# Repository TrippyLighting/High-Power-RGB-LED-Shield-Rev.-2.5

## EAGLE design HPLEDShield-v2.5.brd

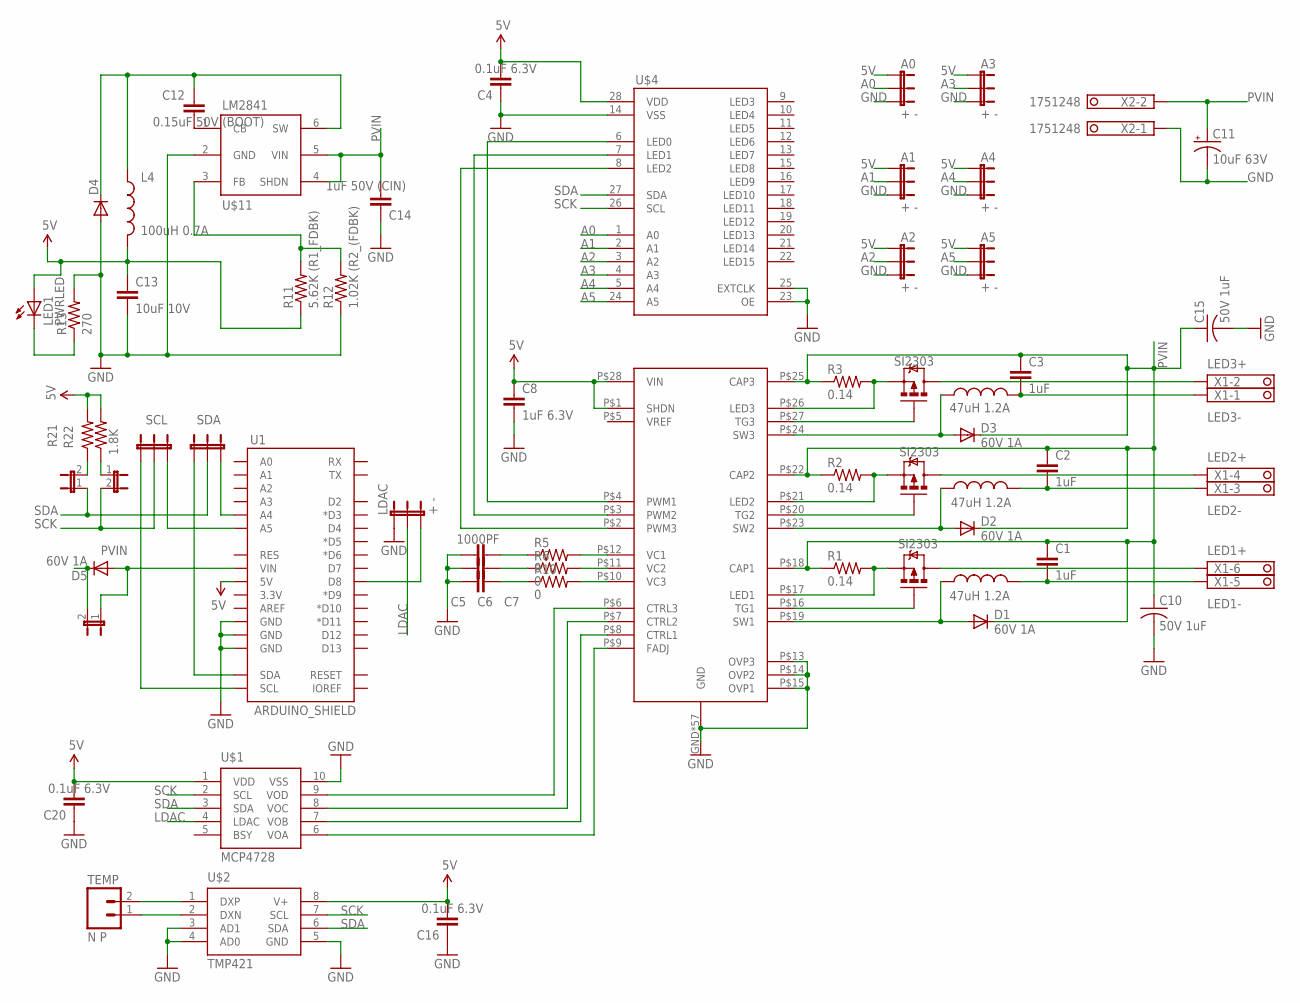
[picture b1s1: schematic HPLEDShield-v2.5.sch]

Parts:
A0, A1, A2, A3, A4, A5: + -; SJ_3
C1, C2, C3: 1uF; 0805
C4, C16, C20: 0.1uF 6.3V; 0402-CAP
C5, C6, C7: 1000PF; 0402-CAP
C8: 1uF 6.3V; 0402-CAP
C10, C15: 50V 1uF; C1210
C11: 10uF 63V; PANASONIC_D
C12: 0.15uF 50V (BOOT); 0603-CAP
C13: 10uF 10V; 0805
C14: 1uF 50V (CIN); 1206
D1, D2, D3, D5: 60V 1A; SOD123
D4: DIODE-SCHOTTKY_ 60V 1A; SOD123
JP1: PWM3; SJ_2S-NO
JP2, JP3: PWM3; SJ_2S
L1, L2, L3: 47uH 1.2A; ELL8TP
L4: 100uH 0.7A; ELL6UH
LDAC: + -; SJ_3
LED1: PWRLED; LED-0603
LT3496: LT3496; LT3694_TSSOP
Q1, Q2, Q3: SI2303; SOT-23
R1, R2, R3: 0.14; 0603-RES
R5, R6, R10: 0; R0402
R11: 5.62K (R1_FDBK); 0603-RES
R12: 1.02K (R2_(FDBK); 0603-RES
R13: 270; 0603-RES
R21, R22: 1.8K; 0402-RES
SCL: JUMPER-3SMD; SJ_3
SDA: JUMPER-3SMD; SJ_3
TEMP: N P; 1X02
U1: ARDUINO_SHIELD; DUEMILANOVE_VIAS
U$1: MCP4728; MSOP10
U$2: TMP421; SOT23-8
U$4: PCA9685; TSSOP28
U$11: LM2841; TSOT-6
X1: LED1+; 1751280
X2: 1751248

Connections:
5V: A0.1, A1.1, A2.1, A3.1, A4.1, A5.1, C4.2, C8.1, C13.1, C16.2, C20.2, L4.P$2 (2), LED1.A, LT3496.P$1 (SHDN), LT3496.P$28 (VIN), R11.1, R21.2, R22.2, U1.5V, U$1.1 (VDD), U$2.8 (V+), U$4.28 (VDD)
A0: A0.2, U$4.1 (A0)
A1: A1.2, U$4.2 (A1)
A2: A2.2, U$4.3 (A2)
A3: A3.2, U$4.4 (A3)
A4: A4.2, U$4.5 (A4)
A5: A5.2, U$4.24 (A5)
GND: A0.3, A1.3, A2.3, A3.3, A4.3, A5.3, C4.1, C5.1, C6.1, C7.1, C8.2, C10.2, C11.-, C13.2, C14.1, C15.2, C16.1, C20.1, D4.2 (A), LDAC.1, LT3496.GND, LT3496.P$13 (OVP3), LT3496.P$14 (OVP2), LT3496.P$15 (OVP1), LT3496.P$29 (GND), LT3496.P$30 (GND), LT3496.P$31 (GND), LT3496.P$32 (GND), LT3496.P$33 (GND), LT3496.P$34 (GND), LT3496.P$35 (GND), LT3496.P$36 (GND), LT3496.P$37 (GND), LT3496.P$38 (GND), LT3496.P$39 (GND), LT3496.P$40 (GND), LT3496.P$41 (GND), LT3496.P$42 (GND), LT3496.P$43 (GND), LT3496.P$44 (GND), LT3496.P$45 (GND), LT3496.P$46 (GND), LT3496.P$47 (GND), LT3496.P$48 (GND), LT3496.P$49 (GND), LT3496.P$50 (GND), LT3496.P$51 (GND), LT3496.P$52 (GND), LT3496.P$53 (GND), LT3496.P$54 (GND), LT3496.P$55 (GND), LT3496.P$56 (GND), LT3496.P$57 (GND), LT3496.P$58 (GND), LT3496.P$59 (GND), LT3496.P$60 (GND), LT3496.P$61 (GND), LT3496.P$62 (GND), LT3496.P$63 (GND), LT3496.P$64 (GND), LT3496.P$65 (GND), LT3496.P$66 (GND), LT3496.P$67 (GND), LT3496.P$68 (GND), LT3496.P$69 (GND), LT3496.P$70 (GND), LT3496.P$71 (GND), LT3496.P$72 (GND), LT3496.P$73 (GND), LT3496.P$74 (GND), LT3496.P$75 (GND), LT3496.P$76 (GND), LT3496.P$77 (GND), LT3496.P$78 (GND), LT3496.P$79 (GND), LT3496.P$80 (GND), LT3496.P$81 (GND), LT3496.P$82 (GND), LT3496.P$83 (GND), LT3496.P$84 (GND), R12.1, R13.2, U1.GND@0 (GND), U1.GND@1 (GND), U1.GND@2 (GND), U$1.10 (VSS), U$2.3 (AD1), U$2.4 (AD0), U$2.5 (GND), U$4.14 (VSS), U$4.23 (OE), U$4.25 (EXTCLK), U$11.2 (GND), X2.1
LDAC: LDAC.2, U$1.4 (LDAC)
unnamed: JP2.2, R21.1
unnamed: JP3.1, R22.1
unnamed: LT3496.P$12 (VC1), R5.2
unnamed: LT3496.P$11 (VC2), R6.2
unnamed: LT3496.P$10 (VC3), R10.2
unnamed: C7.2, R5.1
unnamed: LDAC.3, U1.D8
unnamed: C6.2, R6.1
unnamed: C5.2, R10.1
unnamed: LT3496.P$8 (CTRL1), U$1.7 (VOB)
unnamed: TEMP.2, U$2.1 (DXP)
unnamed: TEMP.1, U$2.2 (DXN)
unnamed: C12.1, D4.1 (C), L4.P$1 (1), U$11.6 (SW)
unnamed: LT3496.P$7 (CTRL2), U$1.8 (VOC)
unnamed: LT3496.P$21 (LED2), Q2.2 (S), R2.2
unnamed: LT3496.P$9 (FADJ), U$1.6 (VOA)
unnamed: LT3496.P$26 (LED3), Q3.2 (S), R3.2
unnamed: LT3496.P$27 (TG3), Q3.1 (G)
unnamed: LT3496.P$6 (CTRL3), U$1.9 (VOD)
unnamed: D3.2 (A), L3.P$1 (1), LT3496.P$24 (SW3)
unnamed: C1.2, L1.P$2 (2), X1.5
unnamed: LED1.C, R13.1
unnamed: C12.2, U$11.1 (CB)
unnamed: SDA.1, U1.SDA
unnamed: SCL.1, U1.SCL
unnamed: SDA.3, U1.A4
unnamed: SCL.3, U1.A5
unnamed: R11.2, R12.2, U$11.3 (FB)
unnamed: D2.2 (A), L2.P$1 (1), LT3496.P$23 (SW2)
unnamed: Q3.3 (D), X1.2
unnamed: D1.2 (A), L1.P$1 (1), LT3496.P$19 (SW1)
unnamed: LT3496.P$20 (TG2), Q2.1 (G)
unnamed: C3.2, L3.P$2 (2), X1.1
unnamed: LT3496.P$17 (LED1), Q1.2 (S), R1.2
unnamed: LT3496.P$16 (TG1), Q1.1 (G)
unnamed: C2.2, L2.P$2 (2), X1.3
unnamed: Q2.3 (D), X1.4
unnamed: Q1.3 (D), X1.6
PVIN: C1.1, C2.1, C3.1, C10.1, C11.+, C14.2, C15.1, D1.1 (C), D2.1 (C), D3.1 (C), D5.1 (C), JP1.2, LT3496.P$18 (CAP1), LT3496.P$22 (CAP2), LT3496.P$25 (CAP3), R1.1, R2.1, R3.1, U$11.4 (SHDN), U$11.5 (VIN), X2.2
PWM1: LT3496.P$4 (PWM1), U$4.6 (LED0)
PWM2: LT3496.P$3 (PWM2), U$4.7 (LED1)
PWM3: LT3496.P$2 (PWM3), U$4.8 (LED2)
SCK: JP3.2, SCL.2, U$1.2 (SCL), U$2.7 (SCL), U$4.26 (SCL)
SDA: JP2.1, SDA.2, U$1.3 (SDA), U$2.6 (SDA), U$4.27 (SDA)
VIN: D5.2 (A), JP1.1, U1.VIN

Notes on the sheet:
LED3+
LED3-
LED2-
LED2+
LED1+
LED1-

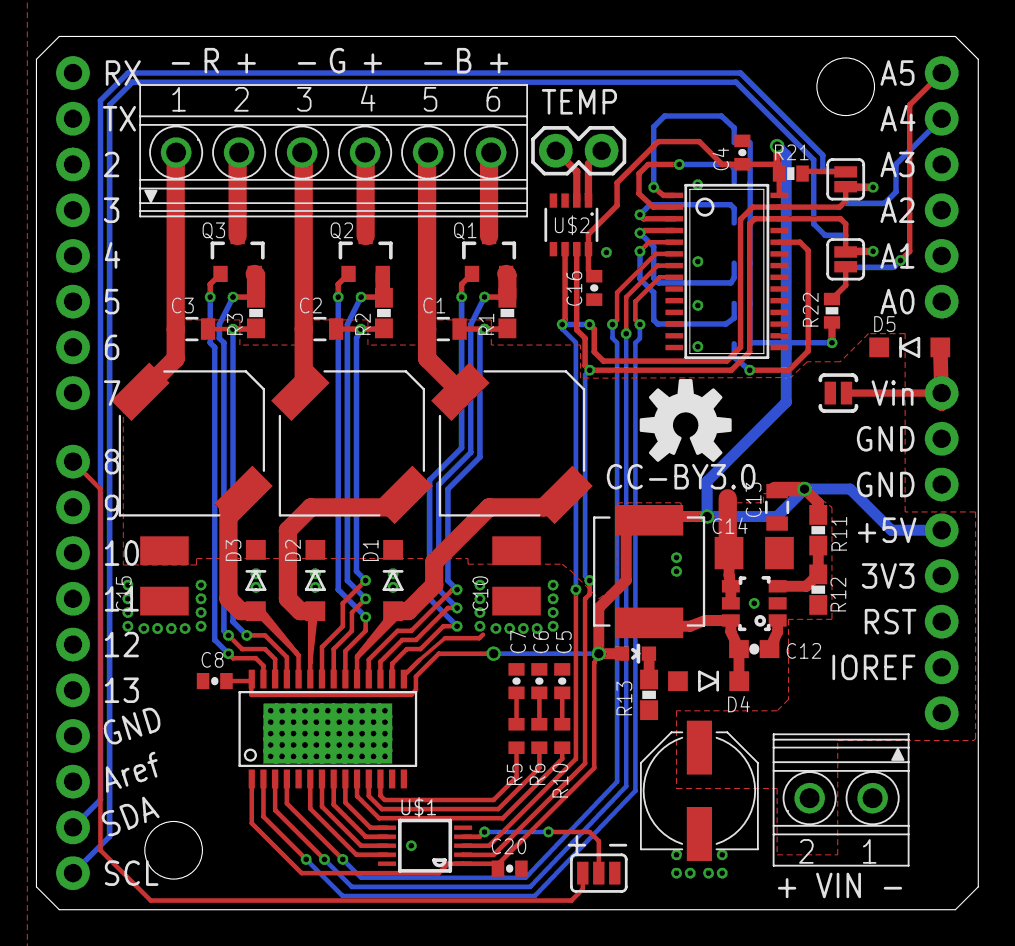
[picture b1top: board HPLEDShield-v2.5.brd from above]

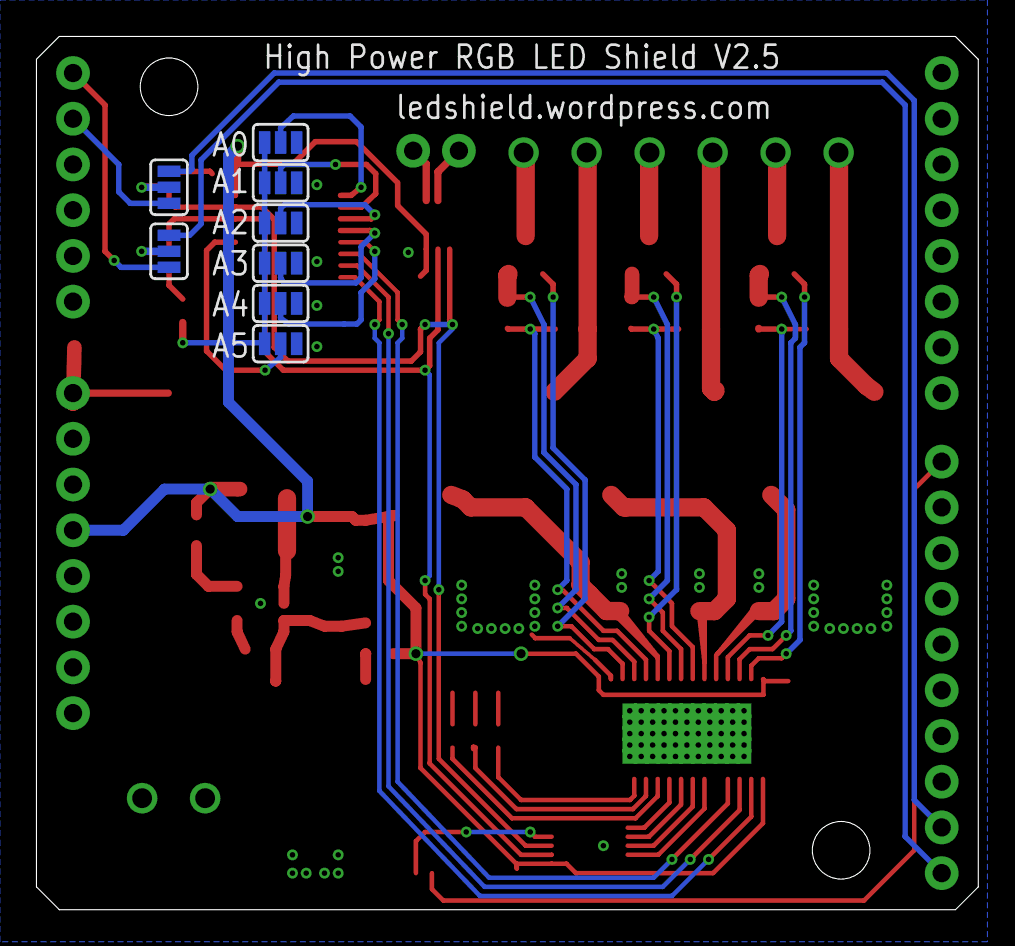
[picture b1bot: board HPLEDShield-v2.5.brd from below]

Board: 2 copper layers, 52.3 x 48.5 mm, 62 parts (8 on the bottom side), 54 nets.

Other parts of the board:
U$7: OSHW-LOGO-M

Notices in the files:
HPLEDShield-v2.5.brd:
CC-BY3.0
